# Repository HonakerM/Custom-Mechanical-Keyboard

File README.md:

# Custom-Mechanical-Keyboard
This repo willl hold all of my files and ideas for my custom made mechanical keyboard

## Keyboard Design
General Layout of my keyboard. Will hopefully be useful to have the extra macros.
http://www.keyboard-layout-editor.com/#/gists/60a0aba0b811de26e8dae9ab40508e25

## Plate Designer
Will be useful later
http://builder.swillkb.com/

## Eagle Library
I edited the key switches to ws2812c's instead of the ws2812b-mini. This library was was needed for the website below
https://github.com/clueboard/eagle_libs

## Eagle Creator
This website generated eagle scripts to position and place pieces. I recommend reorganizing after but it is a good starting point. Especially for the pcb file.
https://kalerator.clueboard.co/

## Useful Doc 
Very useful reddit post about large led arrays.
https://www.reddit.com/r/MechanicalKeyboards/comments/fckxao/custom_114key_schematic_correct/

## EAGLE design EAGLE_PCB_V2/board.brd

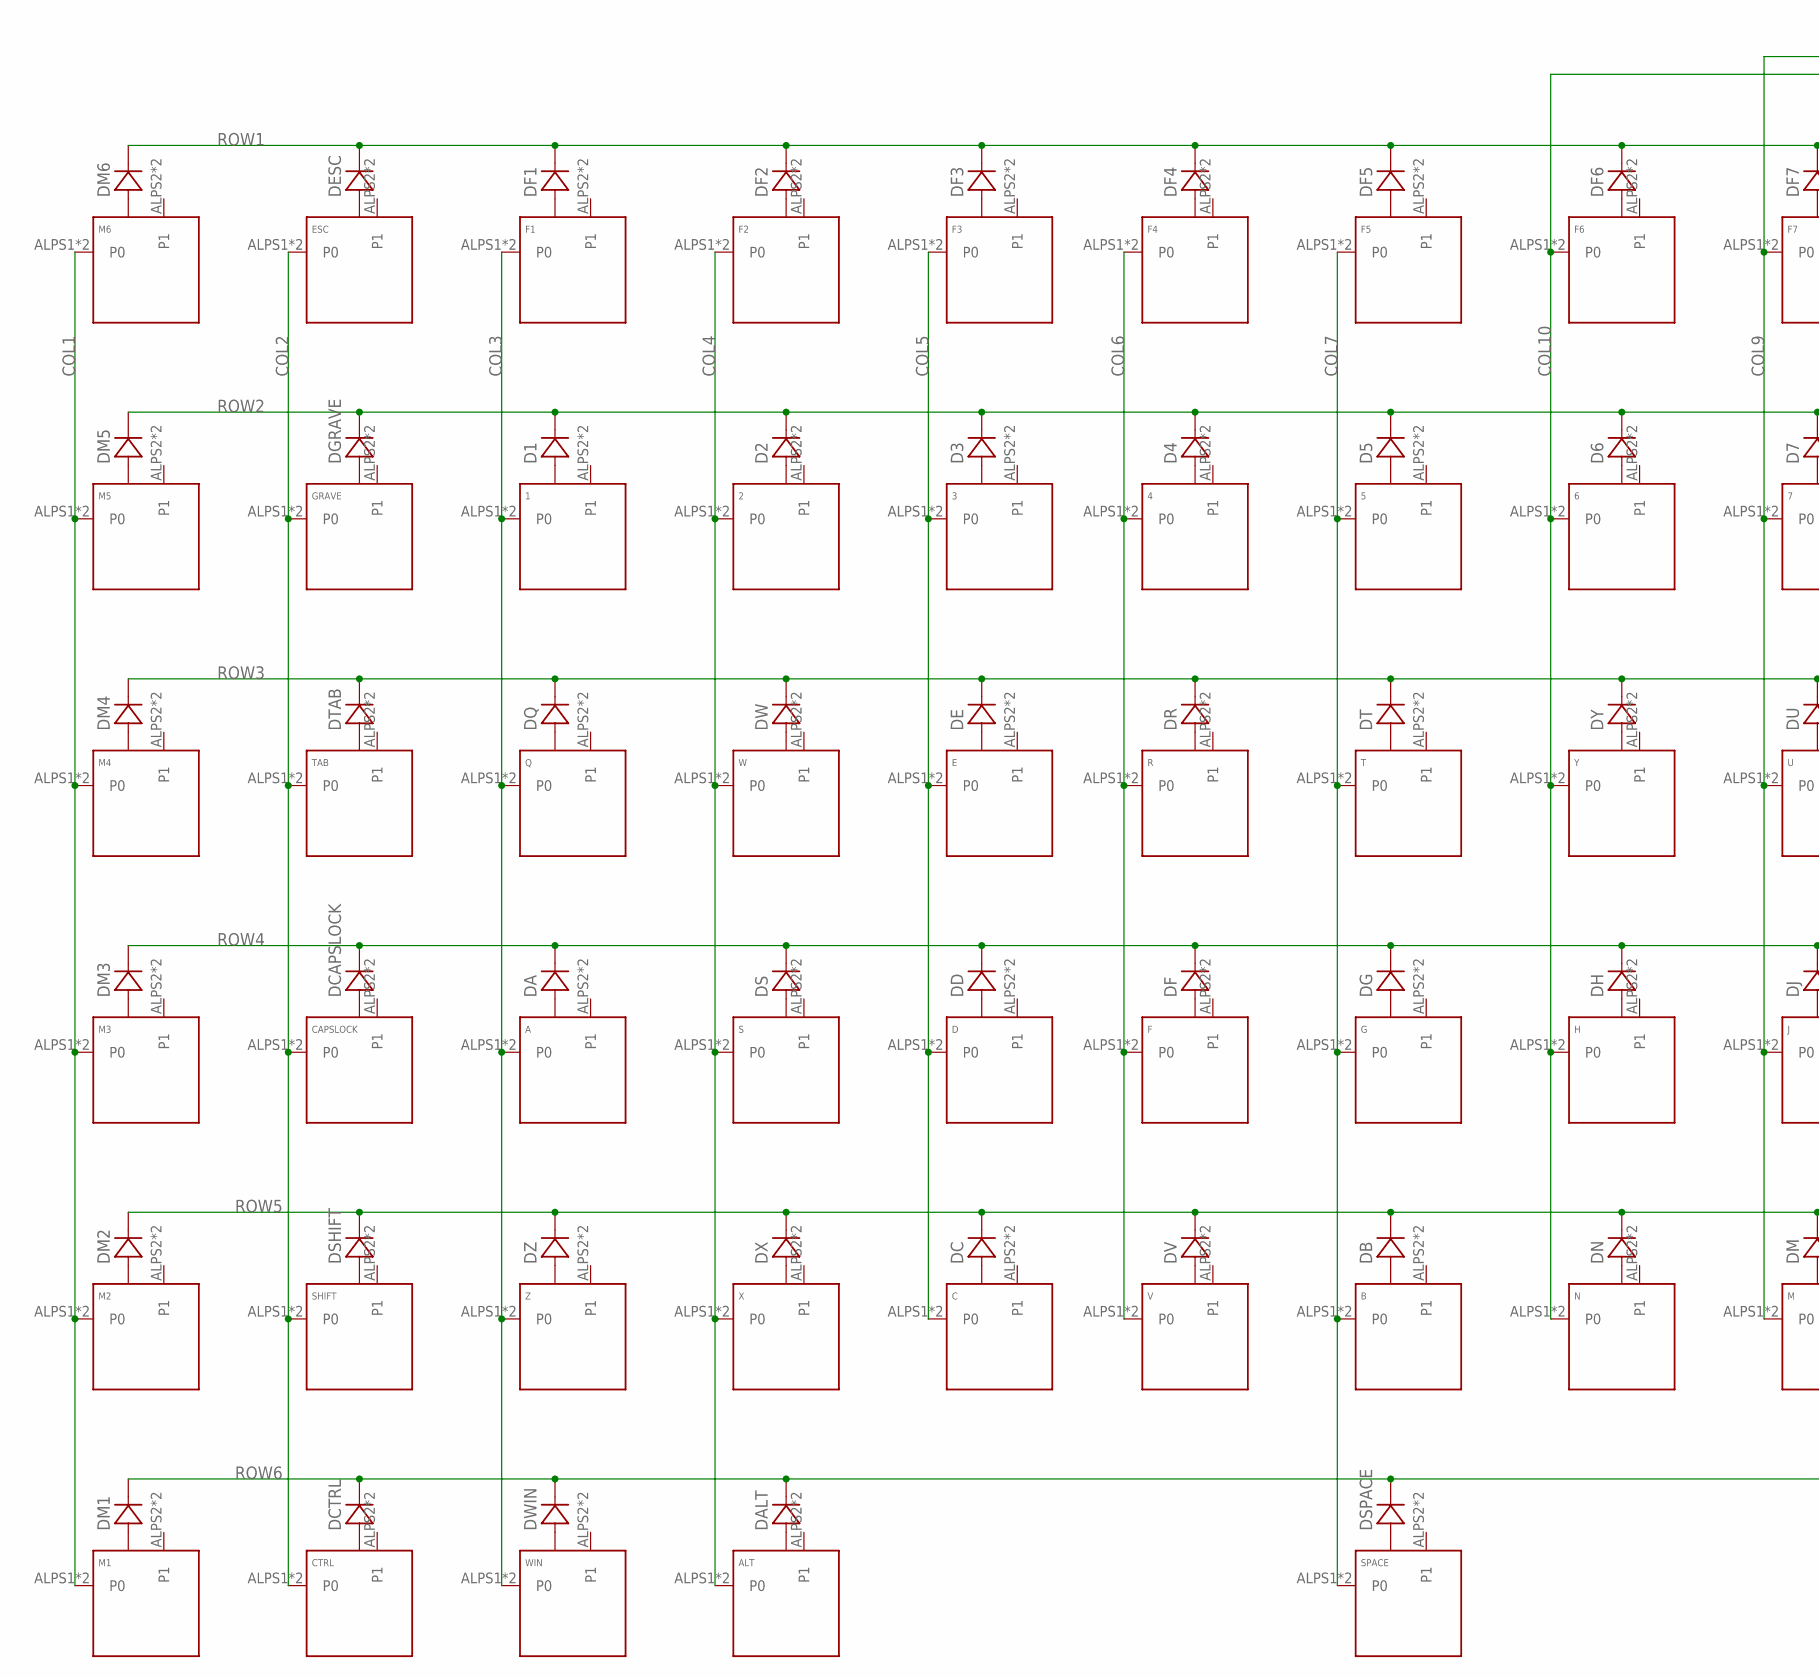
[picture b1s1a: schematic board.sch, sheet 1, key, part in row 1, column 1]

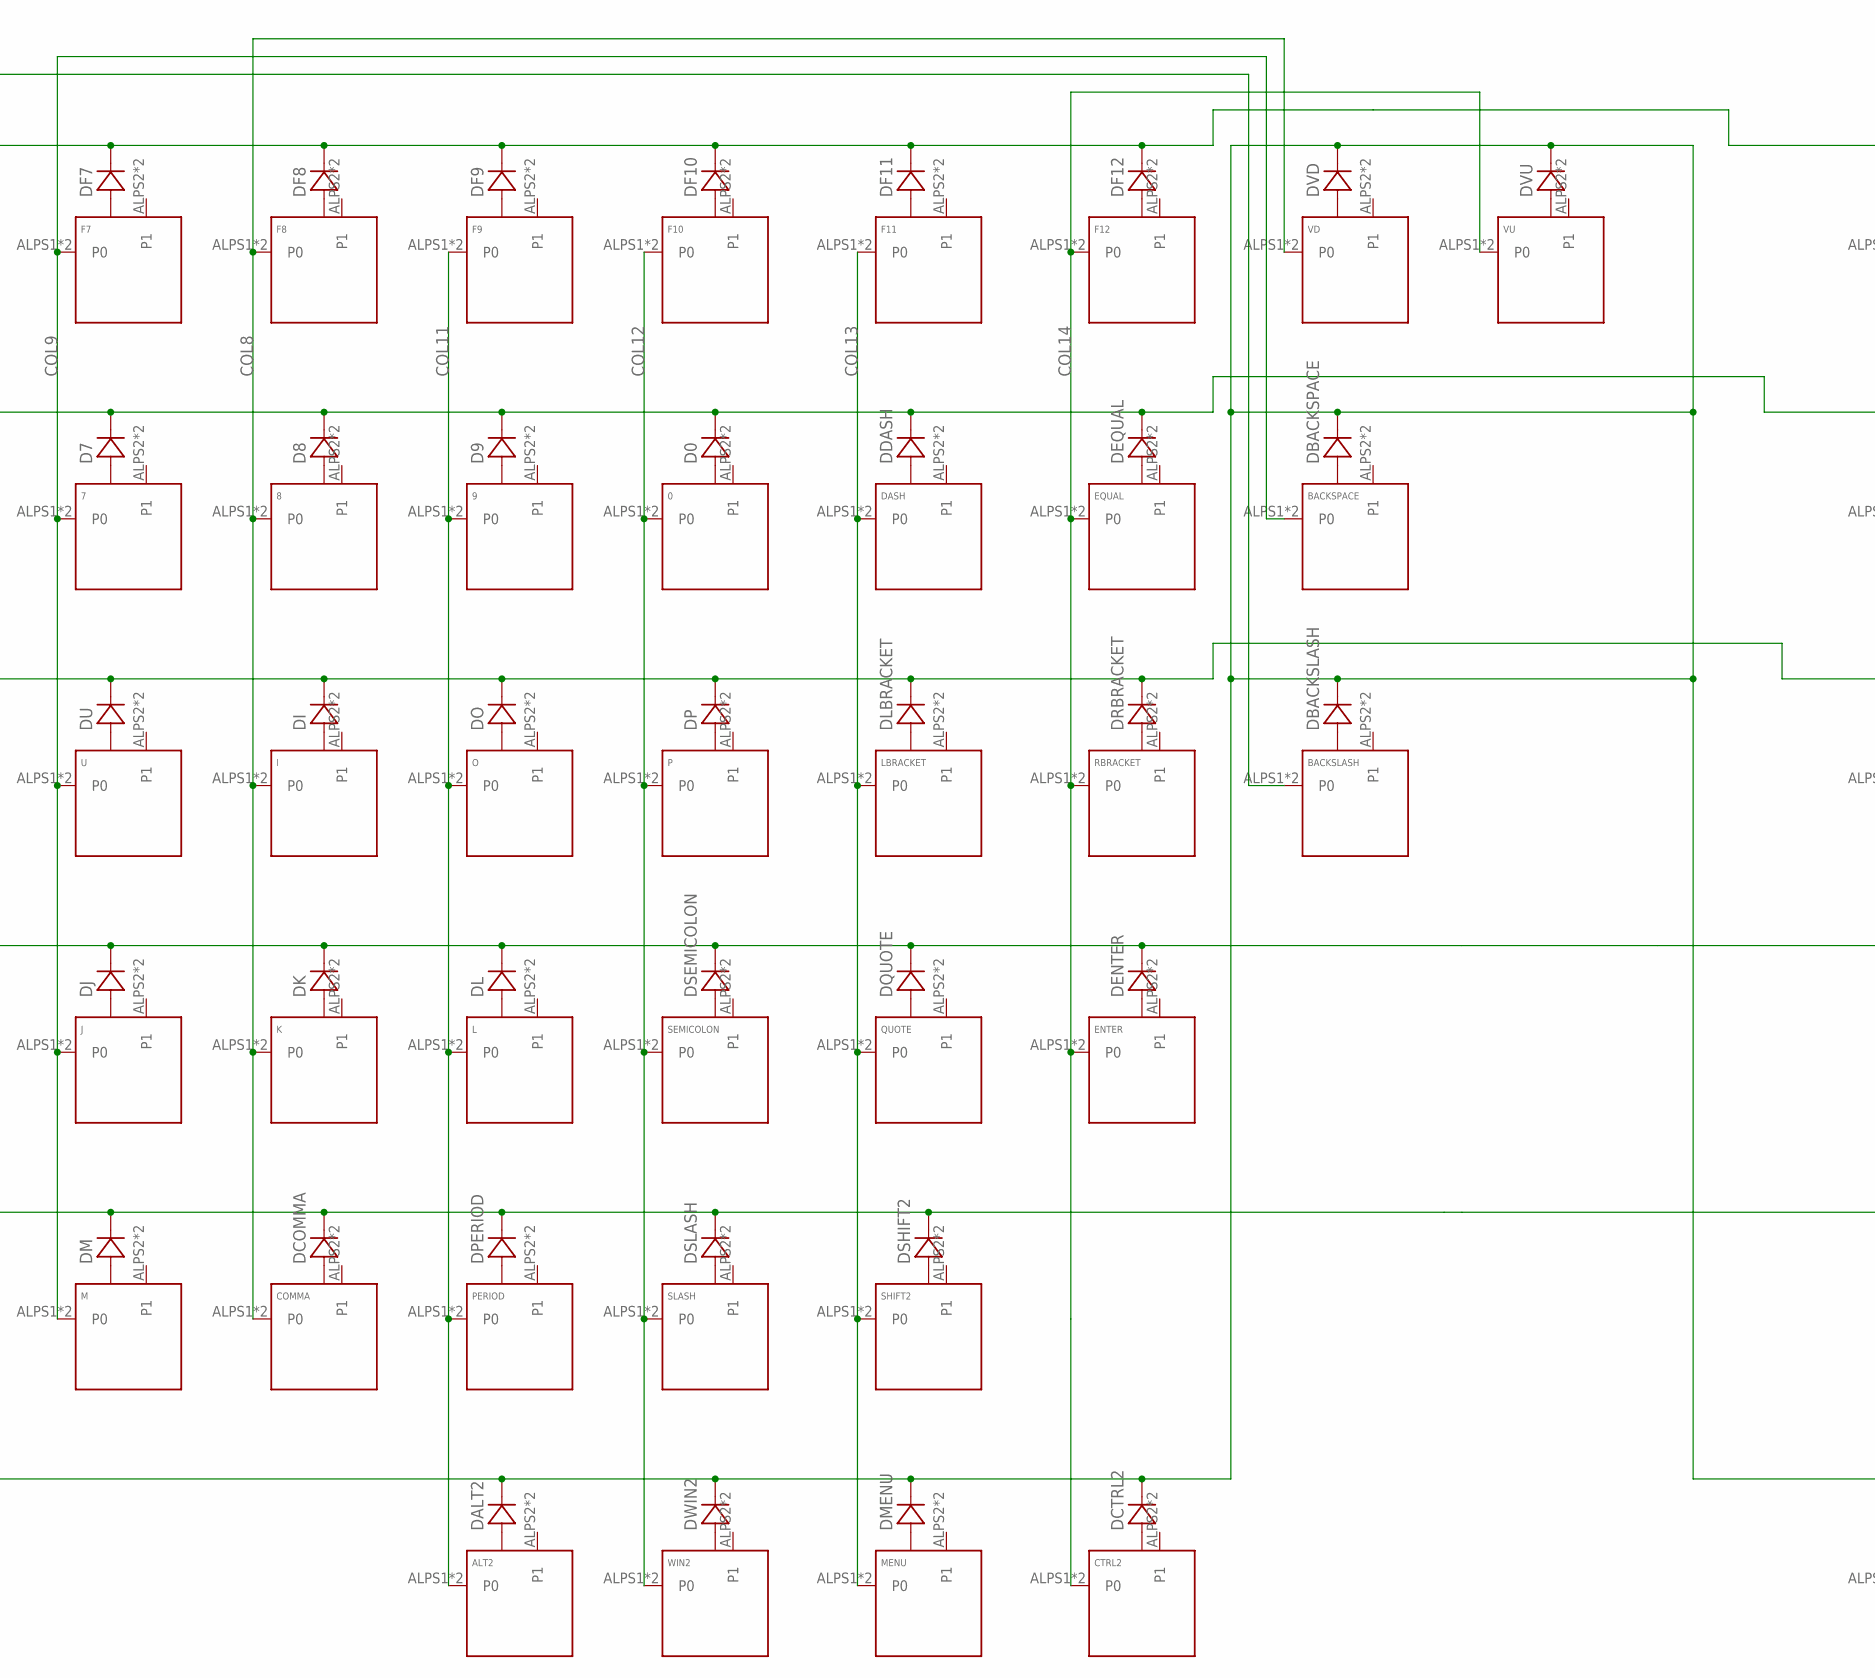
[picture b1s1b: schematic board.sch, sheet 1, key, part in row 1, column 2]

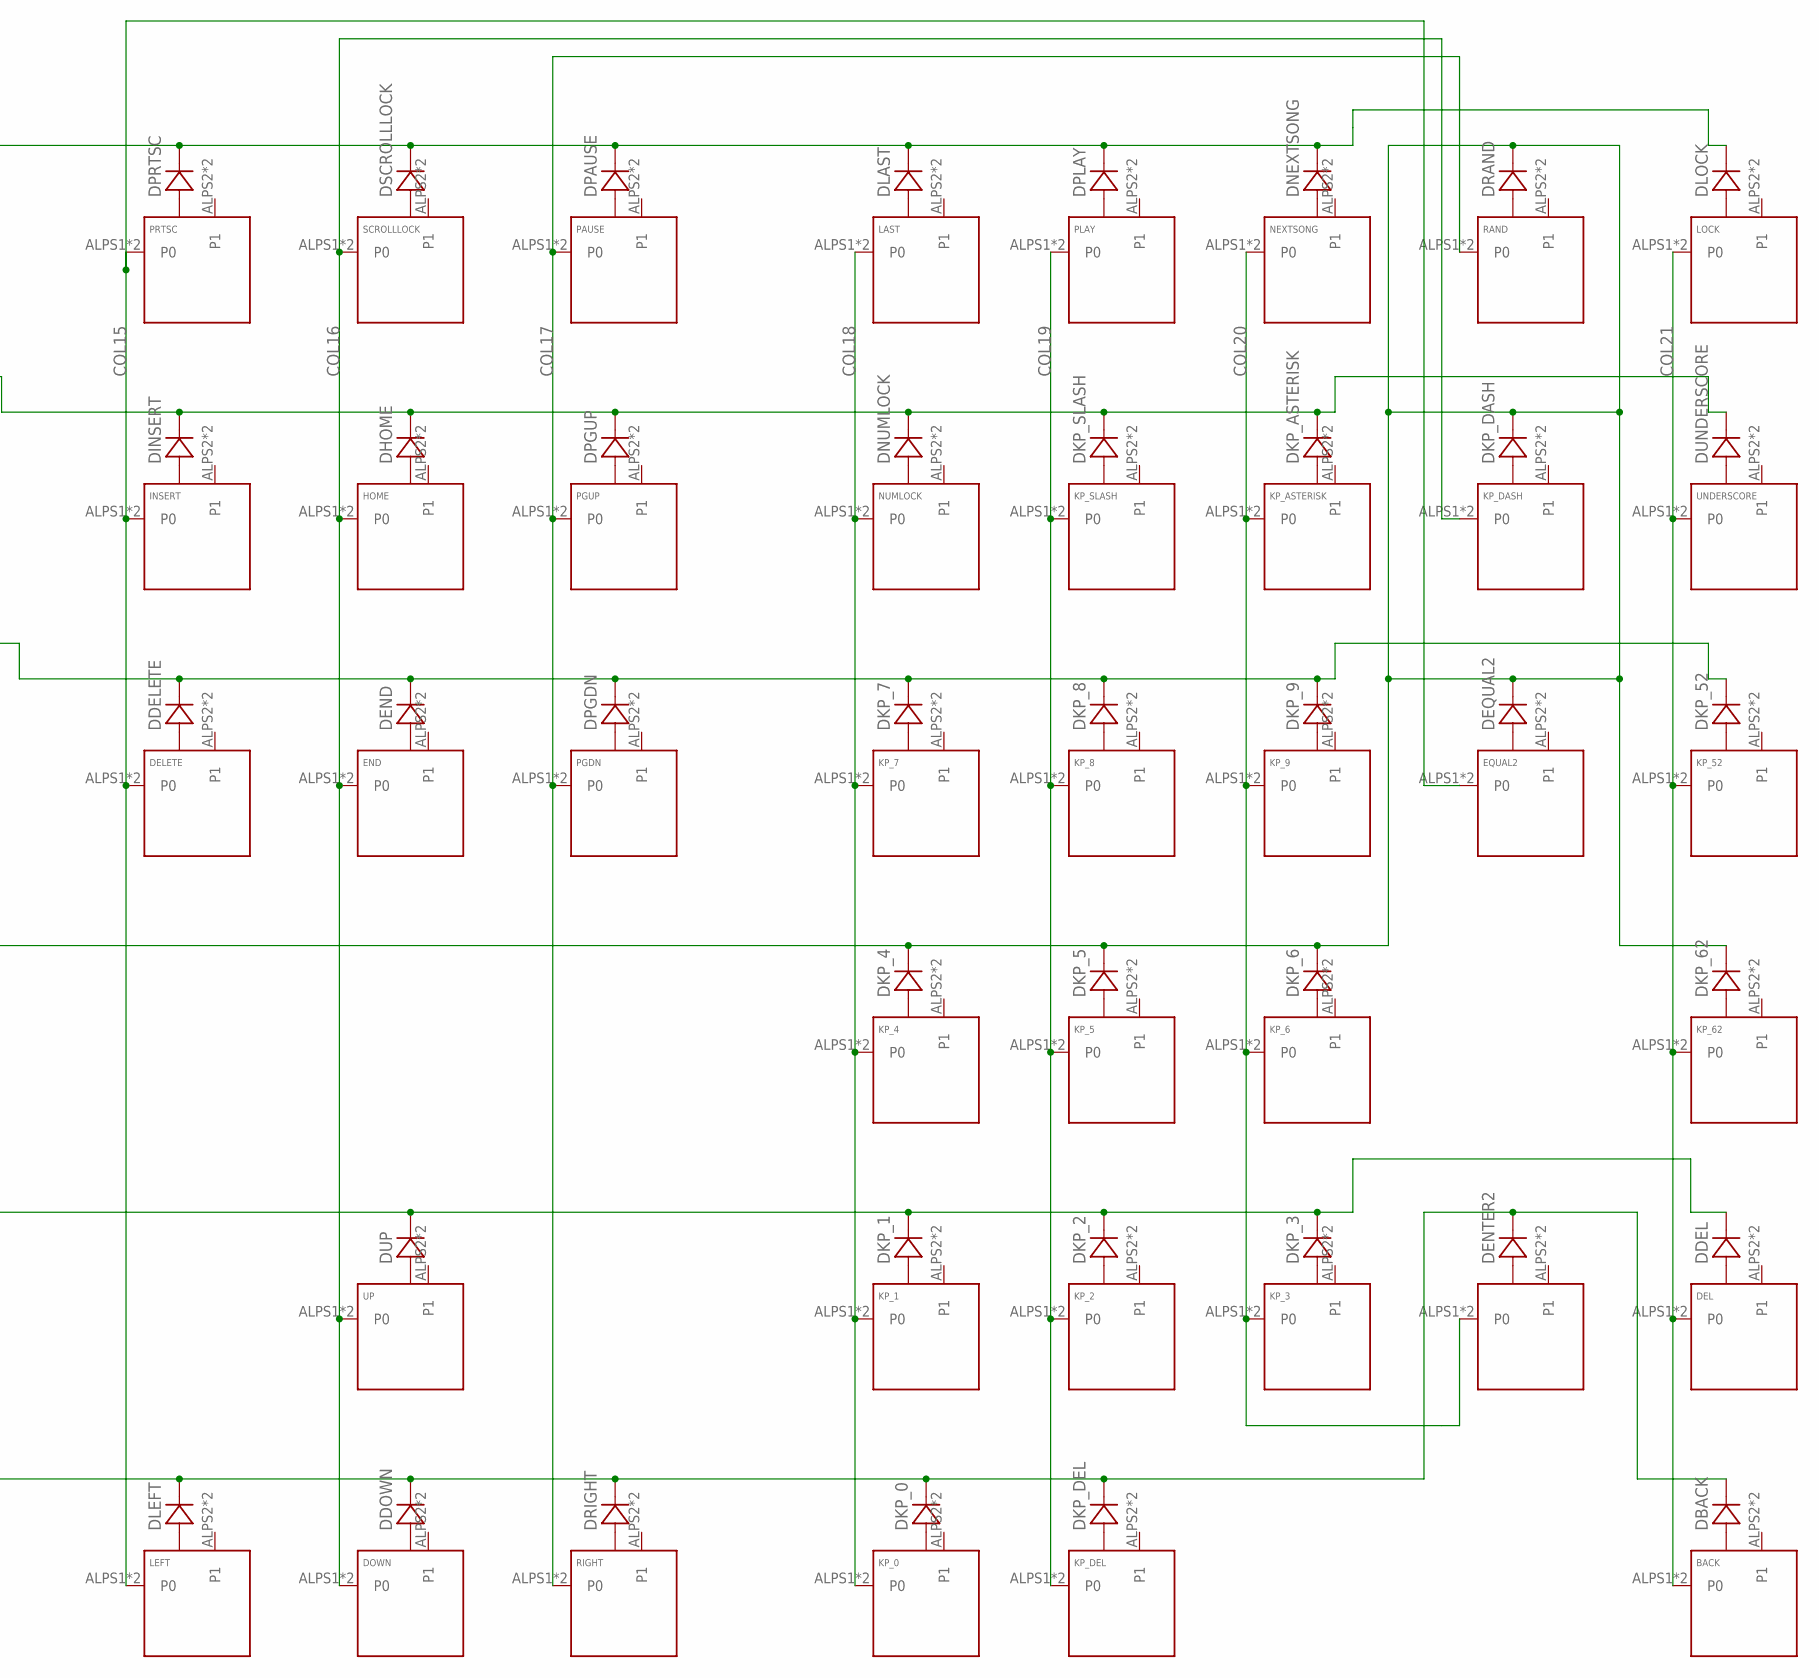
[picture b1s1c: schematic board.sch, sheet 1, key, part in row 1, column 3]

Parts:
0, 1, 2, 3, 4, 5, 6, 7, 8, 9: KEYSWITCH-PLAIN-ALPSMX-1U; ALPSMX-1U
A: KEYSWITCH-PLAIN-ALPSMX-1U; ALPSMX-1U
ALT, ALT2: KEYSWITCH-PLAIN-ALPSMX-1U; ALPSMX-1U
B: KEYSWITCH-PLAIN-ALPSMX-1U; ALPSMX-1U
BACK: KEYSWITCH-PLAIN-ALPSMX-1U; ALPSMX-1U
BACKSLASH: KEYSWITCH-PLAIN-ALPSMX-1U; ALPSMX-1U
BACKSPACE: KEYSWITCH-PLAIN-ALPSMX-2U; ALPSMX-2U
C: KEYSWITCH-PLAIN-ALPSMX-1U; ALPSMX-1U
CAPSLOCK: KEYSWITCH-PLAIN-ALPSMX-1U; ALPSMX-1U
COMMA: KEYSWITCH-PLAIN-ALPSMX-1U; ALPSMX-1U
CTRL, CTRL2: KEYSWITCH-PLAIN-ALPSMX-1U; ALPSMX-1U
D: KEYSWITCH-PLAIN-ALPSMX-1U; ALPSMX-1U
D0, D1, D2, D3, D4, D5, D6, D7, D8, D9: DIODE-SOD-123; SOD-123
DA: DIODE-SOD-123; SOD-123
DALT, DALT2: DIODE-SOD-123; SOD-123
DASH: KEYSWITCH-PLAIN-ALPSMX-1U; ALPSMX-1U
DB: DIODE-SOD-123; SOD-123
DBACK: DIODE-SOD-123; SOD-123
DBACKSLASH: DIODE-SOD-123; SOD-123
DBACKSPACE: DIODE-SOD-123; SOD-123
DC: DIODE-SOD-123; SOD-123
DCAPSLOCK: DIODE-SOD-123; SOD-123
DCOMMA: DIODE-SOD-123; SOD-123
DCTRL, DCTRL2: DIODE-SOD-123; SOD-123
DD: DIODE-SOD-123; SOD-123
DDASH: DIODE-SOD-123; SOD-123
DDEL: DIODE-SOD-123; SOD-123
DDELETE: DIODE-SOD-123; SOD-123
DDOWN: DIODE-SOD-123; SOD-123
DE: DIODE-SOD-123; SOD-123
DEL: KEYSWITCH-PLAIN-ALPSMX-1U; ALPSMX-1U
DELETE: KEYSWITCH-PLAIN-ALPSMX-1U; ALPSMX-1U
DEND: DIODE-SOD-123; SOD-123
DENTER, DENTER2: DIODE-SOD-123; SOD-123
DEQUAL, DEQUAL2: DIODE-SOD-123; SOD-123
DESC: DIODE-SOD-123; SOD-123
DF, DF1, DF2, DF3, DF4, DF5, DF6, DF7, DF8, DF9, DF10, DF11, DF12: DIODE-SOD-123; SOD-123
DG: DIODE-SOD-123; SOD-123
DGRAVE: DIODE-SOD-123; SOD-123
DH: DIODE-SOD-123; SOD-123
DHOME: DIODE-SOD-123; SOD-123
DI: DIODE-SOD-123; SOD-123
DINSERT: DIODE-SOD-123; SOD-123
DJ: DIODE-SOD-123; SOD-123
DK: DIODE-SOD-123; SOD-123
DKP_0, DKP_1, DKP_2, DKP_3, DKP_4, DKP_5, DKP_6, DKP_7, DKP_8, DKP_9, DKP_52, DKP_62: DIODE-SOD-123; SOD-123
DKP_ASTERISK: DIODE-SOD-123; SOD-123
DKP_DASH: DIODE-SOD-123; SOD-123
DKP_DEL: DIODE-SOD-123; SOD-123
DKP_SLASH: DIODE-SOD-123; SOD-123
DL: DIODE-SOD-123; SOD-123
DLAST: DIODE-SOD-123; SOD-123
DLBRACKET: DIODE-SOD-123; SOD-123
DLEFT: DIODE-SOD-123; SOD-123
DLOCK: DIODE-SOD-123; SOD-123
DM, DM1, DM2, DM3, DM4, DM5, DM6: DIODE-SOD-123; SOD-123
DMENU: DIODE-SOD-123; SOD-123
DN: DIODE-SOD-123; SOD-123
DNEXTSONG: DIODE-SOD-123; SOD-123
DNUMLOCK: DIODE-SOD-123; SOD-123
DO: DIODE-SOD-123; SOD-123
DOWN: KEYSWITCH-PLAIN-ALPSMX-1U; ALPSMX-1U
DP: DIODE-SOD-123; SOD-123
DPAUSE: DIODE-SOD-123; SOD-123
DPERIOD: DIODE-SOD-123; SOD-123
DPGDN: DIODE-SOD-123; SOD-123
DPGUP: DIODE-SOD-123; SOD-123
DPLAY: DIODE-SOD-123; SOD-123
DPRTSC: DIODE-SOD-123; SOD-123
DQ: DIODE-SOD-123; SOD-123
DQUOTE: DIODE-SOD-123; SOD-123
DR: DIODE-SOD-123; SOD-123
DRAND: DIODE-SOD-123; SOD-123
DRBRACKET: DIODE-SOD-123; SOD-123
DRIGHT: DIODE-SOD-123; SOD-123
DS: DIODE-SOD-123; SOD-123
DSCROLLLOCK: DIODE-SOD-123; SOD-123
DSEMICOLON: DIODE-SOD-123; SOD-123
DSHIFT, DSHIFT2: DIODE-SOD-123; SOD-123
DSLASH: DIODE-SOD-123; SOD-123
DSPACE: DIODE-SOD-123; SOD-123
DT: DIODE-SOD-123; SOD-123
DTAB: DIODE-SOD-123; SOD-123
DU: DIODE-SOD-123; SOD-123
DUNDERSCORE: DIODE-SOD-123; SOD-123
DUP: DIODE-SOD-123; SOD-123
DV: DIODE-SOD-123; SOD-123
DVD: DIODE-SOD-123; SOD-123
DVU: DIODE-SOD-123; SOD-123
DW: DIODE-SOD-123; SOD-123
DWIN, DWIN2: DIODE-SOD-123; SOD-123
DX: DIODE-SOD-123; SOD-123
DY: DIODE-SOD-123; SOD-123
DZ: DIODE-SOD-123; SOD-123
E: KEYSWITCH-PLAIN-ALPSMX-1U; ALPSMX-1U
END: KEYSWITCH-PLAIN-ALPSMX-1U; ALPSMX-1U
ENTER: KEYSWITCH-PLAIN-ALPSMX-2U; ALPSMX-2U
ENTER2: KEYSWITCH-PLAIN-ALPSMX-1U; ALPSMX-1U
EQUAL, EQUAL2: KEYSWITCH-PLAIN-ALPSMX-1U; ALPSMX-1U
ESC: KEYSWITCH-PLAIN-ALPSMX-1U; ALPSMX-1U
F, F1, F2, F3, F4, F5, F6, F7, F8, F9, F10, F11, F12: KEYSWITCH-PLAIN-ALPSMX-1U; ALPSMX-1U
G: KEYSWITCH-PLAIN-ALPSMX-1U; ALPSMX-1U
GRAVE: KEYSWITCH-PLAIN-ALPSMX-1U; ALPSMX-1U
H: KEYSWITCH-PLAIN-ALPSMX-1U; ALPSMX-1U
HOME: KEYSWITCH-PLAIN-ALPSMX-1U; ALPSMX-1U
I: KEYSWITCH-PLAIN-ALPSMX-1U; ALPSMX-1U
INSERT: KEYSWITCH-PLAIN-ALPSMX-1U; ALPSMX-1U
J: KEYSWITCH-PLAIN-ALPSMX-1U; ALPSMX-1U
K: KEYSWITCH-PLAIN-ALPSMX-1U; ALPSMX-1U
KP_0: KEYSWITCH-PLAIN-ALPSMX-2U; ALPSMX-2U
KP_1, KP_2, KP_3, KP_4, KP_5, KP_6, KP_7, KP_8, KP_9, KP_52, KP_62: KEYSWITCH-PLAIN-ALPSMX-1U; ALPSMX-1U
KP_ASTERISK: KEYSWITCH-PLAIN-ALPSMX-1U; ALPSMX-1U
KP_DASH: KEYSWITCH-PLAIN-ALPSMX-1U; ALPSMX-1U
KP_DEL: KEYSWITCH-PLAIN-ALPSMX-1U; ALPSMX-1U
KP_SLASH: KEYSWITCH-PLAIN-ALPSMX-1U; ALPSMX-1U
L: KEYSWITCH-PLAIN-ALPSMX-1U; ALPSMX-1U
LAST: KEYSWITCH-PLAIN-ALPSMX-1U; ALPSMX-1U
LBRACKET: KEYSWITCH-PLAIN-ALPSMX-1U; ALPSMX-1U
LEFT: KEYSWITCH-PLAIN-ALPSMX-1U; ALPSMX-1U
LOCK: KEYSWITCH-PLAIN-ALPSMX-1U; ALPSMX-1U
M, M1, M2, M3, M4, M5, M6: KEYSWITCH-PLAIN-ALPSMX-1U; ALPSMX-1U
MENU: KEYSWITCH-PLAIN-ALPSMX-1U; ALPSMX-1U
N: KEYSWITCH-PLAIN-ALPSMX-1U; ALPSMX-1U
NEXTSONG: KEYSWITCH-PLAIN-ALPSMX-1U; ALPSMX-1U
NUMLOCK: KEYSWITCH-PLAIN-ALPSMX-1U; ALPSMX-1U
O: KEYSWITCH-PLAIN-ALPSMX-1U; ALPSMX-1U
P: KEYSWITCH-PLAIN-ALPSMX-1U; ALPSMX-1U
PAUSE: KEYSWITCH-PLAIN-ALPSMX-1U; ALPSMX-1U
PERIOD: KEYSWITCH-PLAIN-ALPSMX-1U; ALPSMX-1U
PGDN: KEYSWITCH-PLAIN-ALPSMX-1U; ALPSMX-1U
PGUP: KEYSWITCH-PLAIN-ALPSMX-1U; ALPSMX-1U
PLAY: KEYSWITCH-PLAIN-ALPSMX-1U; ALPSMX-1U
PRTSC: KEYSWITCH-PLAIN-ALPSMX-1U; ALPSMX-1U
Q: KEYSWITCH-PLAIN-ALPSMX-1U; ALPSMX-1U
QUOTE: KEYSWITCH-PLAIN-ALPSMX-1U; ALPSMX-1U
R: KEYSWITCH-PLAIN-ALPSMX-1U; ALPSMX-1U
RAND: KEYSWITCH-PLAIN-ALPSMX-1U; ALPSMX-1U
RBRACKET: KEYSWITCH-PLAIN-ALPSMX-1U; ALPSMX-1U
RIGHT: KEYSWITCH-PLAIN-ALPSMX-1U; ALPSMX-1U
S: KEYSWITCH-PLAIN-ALPSMX-1U; ALPSMX-1U
SCROLLLOCK: KEYSWITCH-PLAIN-ALPSMX-1U; ALPSMX-1U
SEMICOLON: KEYSWITCH-PLAIN-ALPSMX-1U; ALPSMX-1U
SHIFT, SHIFT2: KEYSWITCH-PLAIN-ALPSMX-2U; ALPSMX-2U
SLASH: KEYSWITCH-PLAIN-ALPSMX-1U; ALPSMX-1U
SPACE: KEYSWITCH-PLAIN-ALPSMX-6.25U; ALPSMX-6.25U
T: KEYSWITCH-PLAIN-ALPSMX-1U; ALPSMX-1U
TAB: KEYSWITCH-PLAIN-ALPSMX-1U; ALPSMX-1U
U: KEYSWITCH-PLAIN-ALPSMX-1U; ALPSMX-1U
UNDERSCORE: KEYSWITCH-PLAIN-ALPSMX-1U; ALPSMX-1U
UP: KEYSWITCH-PLAIN-ALPSMX-1U; ALPSMX-1U
V: KEYSWITCH-PLAIN-ALPSMX-1U; ALPSMX-1U
VD: KEYSWITCH-PLAIN-ALPSMX-1U; ALPSMX-1U
VU: KEYSWITCH-PLAIN-ALPSMX-1U; ALPSMX-1U
W: KEYSWITCH-PLAIN-ALPSMX-1U; ALPSMX-1U
WIN, WIN2: KEYSWITCH-PLAIN-ALPSMX-1U; ALPSMX-1U
X: KEYSWITCH-PLAIN-ALPSMX-1U; ALPSMX-1U
Y: KEYSWITCH-PLAIN-ALPSMX-1U; ALPSMX-1U
Z: KEYSWITCH-PLAIN-ALPSMX-1U; ALPSMX-1U

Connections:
COL1: M1.ALPS1 (P0), M1.MX1 (P0), M2.ALPS1 (P0), M2.MX1 (P0), M3.ALPS1 (P0), M3.MX1 (P0), M4.ALPS1 (P0), M4.MX1 (P0), M5.ALPS1 (P0), M5.MX1 (P0), M6.ALPS1 (P0), M6.MX1 (P0); also elsewhere on the board
COL2: CAPSLOCK.ALPS1 (P0), CAPSLOCK.MX1 (P0), CTRL.ALPS1 (P0), CTRL.MX1 (P0), ESC.ALPS1 (P0), ESC.MX1 (P0), GRAVE.ALPS1 (P0), GRAVE.MX1 (P0), SHIFT.ALPS1 (P0), SHIFT.MX1 (P0), TAB.ALPS1 (P0), TAB.MX1 (P0); also elsewhere on the board
COL3: 1.ALPS1 (P0), 1.MX1 (P0), A.ALPS1 (P0), A.MX1 (P0), F1.ALPS1 (P0), F1.MX1 (P0), Q.ALPS1 (P0), Q.MX1 (P0), WIN.ALPS1 (P0), WIN.MX1 (P0), Z.ALPS1 (P0), Z.MX1 (P0); also elsewhere on the board
COL4: 2.ALPS1 (P0), 2.MX1 (P0), ALT.ALPS1 (P0), ALT.MX1 (P0), F2.ALPS1 (P0), F2.MX1 (P0), S.ALPS1 (P0), S.MX1 (P0), W.ALPS1 (P0), W.MX1 (P0), X.ALPS1 (P0), X.MX1 (P0); also elsewhere on the board
COL5: 3.ALPS1 (P0), 3.MX1 (P0), C.ALPS1 (P0), C.MX1 (P0), D.ALPS1 (P0), D.MX1 (P0), E.ALPS1 (P0), E.MX1 (P0), F3.ALPS1 (P0), F3.MX1 (P0); also elsewhere on the board
COL6: 4.ALPS1 (P0), 4.MX1 (P0), F.ALPS1 (P0), F.MX1 (P0), F4.ALPS1 (P0), F4.MX1 (P0), R.ALPS1 (P0), R.MX1 (P0), V.ALPS1 (P0), V.MX1 (P0); also elsewhere on the board
COL7: 5.ALPS1 (P0), 5.MX1 (P0), B.ALPS1 (P0), B.MX1 (P0), F5.ALPS1 (P0), F5.MX1 (P0), G.ALPS1 (P0), G.MX1 (P0), SPACE.ALPS1 (P0), SPACE.MX1 (P0), T.ALPS1 (P0), T.MX1 (P0); also elsewhere on the board
COL8: 8.ALPS1 (P0), 8.MX1 (P0), COMMA.ALPS1 (P0), COMMA.MX1 (P0), F8.ALPS1 (P0), F8.MX1 (P0), I.ALPS1 (P0), I.MX1 (P0), K.ALPS1 (P0), K.MX1 (P0), VD.ALPS1 (P0), VD.MX1 (P0); also elsewhere on the board
COL9: 7.ALPS1 (P0), 7.MX1 (P0), BACKSPACE.ALPS1 (P0), BACKSPACE.MX1 (P0), F7.ALPS1 (P0), F7.MX1 (P0), J.ALPS1 (P0), J.MX1 (P0), M.ALPS1 (P0), M.MX1 (P0), U.ALPS1 (P0), U.MX1 (P0); also elsewhere on the board
COL10: 6.ALPS1 (P0), 6.MX1 (P0), BACKSLASH.ALPS1 (P0), BACKSLASH.MX1 (P0), F6.ALPS1 (P0), F6.MX1 (P0), H.ALPS1 (P0), H.MX1 (P0), N.ALPS1 (P0), N.MX1 (P0), Y.ALPS1 (P0), Y.MX1 (P0); also elsewhere on the board
COL11: 9.ALPS1 (P0), 9.MX1 (P0), ALT2.ALPS1 (P0), ALT2.MX1 (P0), F9.ALPS1 (P0), F9.MX1 (P0), L.ALPS1 (P0), L.MX1 (P0), O.ALPS1 (P0), O.MX1 (P0), PERIOD.ALPS1 (P0), PERIOD.MX1 (P0); also elsewhere on the board
COL12: 0.ALPS1 (P0), 0.MX1 (P0), F10.ALPS1 (P0), F10.MX1 (P0), P.ALPS1 (P0), P.MX1 (P0), SEMICOLON.ALPS1 (P0), SEMICOLON.MX1 (P0), SLASH.ALPS1 (P0), SLASH.MX1 (P0), WIN2.ALPS1 (P0), WIN2.MX1 (P0); also elsewhere on the board
COL13: DASH.ALPS1 (P0), DASH.MX1 (P0), F11.ALPS1 (P0), F11.MX1 (P0), LBRACKET.ALPS1 (P0), LBRACKET.MX1 (P0), MENU.ALPS1 (P0), MENU.MX1 (P0), QUOTE.ALPS1 (P0), QUOTE.MX1 (P0), SHIFT2.ALPS1 (P0), SHIFT2.MX1 (P0); also elsewhere on the board
COL14: CTRL2.ALPS1 (P0), CTRL2.MX1 (P0), ENTER.ALPS1 (P0), ENTER.MX1 (P0), EQUAL.ALPS1 (P0), EQUAL.MX1 (P0), F12.ALPS1 (P0), F12.MX1 (P0), RBRACKET.ALPS1 (P0), RBRACKET.MX1 (P0), VU.ALPS1 (P0), VU.MX1 (P0); also elsewhere on the board
COL15: DELETE.ALPS1 (P0), DELETE.MX1 (P0), EQUAL2.ALPS1 (P0), EQUAL2.MX1 (P0), INSERT.ALPS1 (P0), INSERT.MX1 (P0), LEFT.ALPS1 (P0), LEFT.MX1 (P0), PRTSC.ALPS1 (P0), PRTSC.MX1 (P0); also elsewhere on the board
COL16: DOWN.ALPS1 (P0), DOWN.MX1 (P0), END.ALPS1 (P0), END.MX1 (P0), HOME.ALPS1 (P0), HOME.MX1 (P0), KP_DASH.ALPS1 (P0), KP_DASH.MX1 (P0), SCROLLLOCK.ALPS1 (P0), SCROLLLOCK.MX1 (P0), UP.ALPS1 (P0), UP.MX1 (P0); also elsewhere on the board
COL17: PAUSE.ALPS1 (P0), PAUSE.MX1 (P0), PGDN.ALPS1 (P0), PGDN.MX1 (P0), PGUP.ALPS1 (P0), PGUP.MX1 (P0), RAND.ALPS1 (P0), RAND.MX1 (P0), RIGHT.ALPS1 (P0), RIGHT.MX1 (P0); also elsewhere on the board
COL18: KP_0.ALPS1 (P0), KP_0.MX1 (P0), KP_1.ALPS1 (P0), KP_1.MX1 (P0), KP_4.ALPS1 (P0), KP_4.MX1 (P0), KP_7.ALPS1 (P0), KP_7.MX1 (P0), LAST.ALPS1 (P0), LAST.MX1 (P0), NUMLOCK.ALPS1 (P0), NUMLOCK.MX1 (P0); also elsewhere on the board
COL19: KP_2.ALPS1 (P0), KP_2.MX1 (P0), KP_5.ALPS1 (P0), KP_5.MX1 (P0), KP_8.ALPS1 (P0), KP_8.MX1 (P0), KP_DEL.ALPS1 (P0), KP_DEL.MX1 (P0), KP_SLASH.ALPS1 (P0), KP_SLASH.MX1 (P0), PLAY.ALPS1 (P0), PLAY.MX1 (P0); also elsewhere on the board
COL20: ENTER2.ALPS1 (P0), ENTER2.MX1 (P0), KP_3.ALPS1 (P0), KP_3.MX1 (P0), KP_6.ALPS1 (P0), KP_6.MX1 (P0), KP_9.ALPS1 (P0), KP_9.MX1 (P0), KP_ASTERISK.ALPS1 (P0), KP_ASTERISK.MX1 (P0), NEXTSONG.ALPS1 (P0), NEXTSONG.MX1 (P0); also elsewhere on the board
COL21: BACK.ALPS1 (P0), BACK.MX1 (P0), DEL.ALPS1 (P0), DEL.MX1 (P0), KP_52.ALPS1 (P0), KP_52.MX1 (P0), KP_62.ALPS1 (P0), KP_62.MX1 (P0), LOCK.ALPS1 (P0), LOCK.MX1 (P0), UNDERSCORE.ALPS1 (P0), UNDERSCORE.MX1 (P0); also elsewhere on the board
ROW1: DESC.C, DF1.C, DF2.C, DF3.C, DF4.C, DF5.C, DF6.C, DF7.C, DF8.C, DF9.C, DF10.C, DF11.C, DF12.C, DLAST.C, DLOCK.C, DM6.C, DNEXTSONG.C, DPAUSE.C, DPLAY.C, DPRTSC.C, DSCROLLLOCK.C; also elsewhere on the board
ROW2: D0.C, D1.C, D2.C, D3.C, D4.C, D5.C, D6.C, D7.C, D8.C, D9.C, DDASH.C, DEQUAL.C, DGRAVE.C, DHOME.C, DINSERT.C, DKP_ASTERISK.C, DKP_SLASH.C, DM5.C, DNUMLOCK.C, DPGUP.C, DUNDERSCORE.C; also elsewhere on the board
ROW3: DDELETE.C, DE.C, DEND.C, DI.C, DKP_7.C, DKP_8.C, DKP_9.C, DKP_52.C, DLBRACKET.C, DM4.C, DO.C, DP.C, DPGDN.C, DQ.C, DR.C, DRBRACKET.C, DT.C, DTAB.C, DU.C, DW.C, DY.C; also elsewhere on the board
ROW4: DA.C, DCAPSLOCK.C, DD.C, DENTER.C, DEQUAL2.C, DF.C, DG.C, DH.C, DJ.C, DK.C, DKP_4.C, DKP_5.C, DKP_6.C, DKP_62.C, DKP_DASH.C, DL.C, DM3.C, DQUOTE.C, DRAND.C, DS.C, DSEMICOLON.C; also elsewhere on the board
ROW5: DB.C, DC.C, DCOMMA.C, DDEL.C, DKP_1.C, DKP_2.C, DKP_3.C, DM.C, DM2.C, DN.C, DPERIOD.C, DSHIFT.C, DSHIFT2.C, DSLASH.C, DUP.C, DV.C, DX.C, DZ.C; also elsewhere on the board
ROW6: DALT.C, DALT2.C, DBACK.C, DBACKSLASH.C, DBACKSPACE.C, DCTRL.C, DCTRL2.C, DDOWN.C, DENTER2.C, DKP_0.C, DKP_DEL.C, DLEFT.C, DM1.C, DMENU.C, DRIGHT.C, DSPACE.C, DVD.C, DVU.C, DWIN.C, DWIN2.C; also elsewhere on the board

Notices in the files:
parts and their libraries:
SparkFun-Clocks: Licensing: Creative Commons ShareAlike 4.0 International - https://creativecommons.org/licenses/by-sa/4.0
